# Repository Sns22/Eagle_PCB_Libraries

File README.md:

my_Eagle_PCB_Libraries
======================

Set of Eagle libraries collected all over the internet. This is a set of Eagle libraries I have downloaded from whereever I could get them from. Some libraries from popular vendors such as LEMO, Farnell, ADAfruit, Sparkfun. There are also ulp and scr files in here.

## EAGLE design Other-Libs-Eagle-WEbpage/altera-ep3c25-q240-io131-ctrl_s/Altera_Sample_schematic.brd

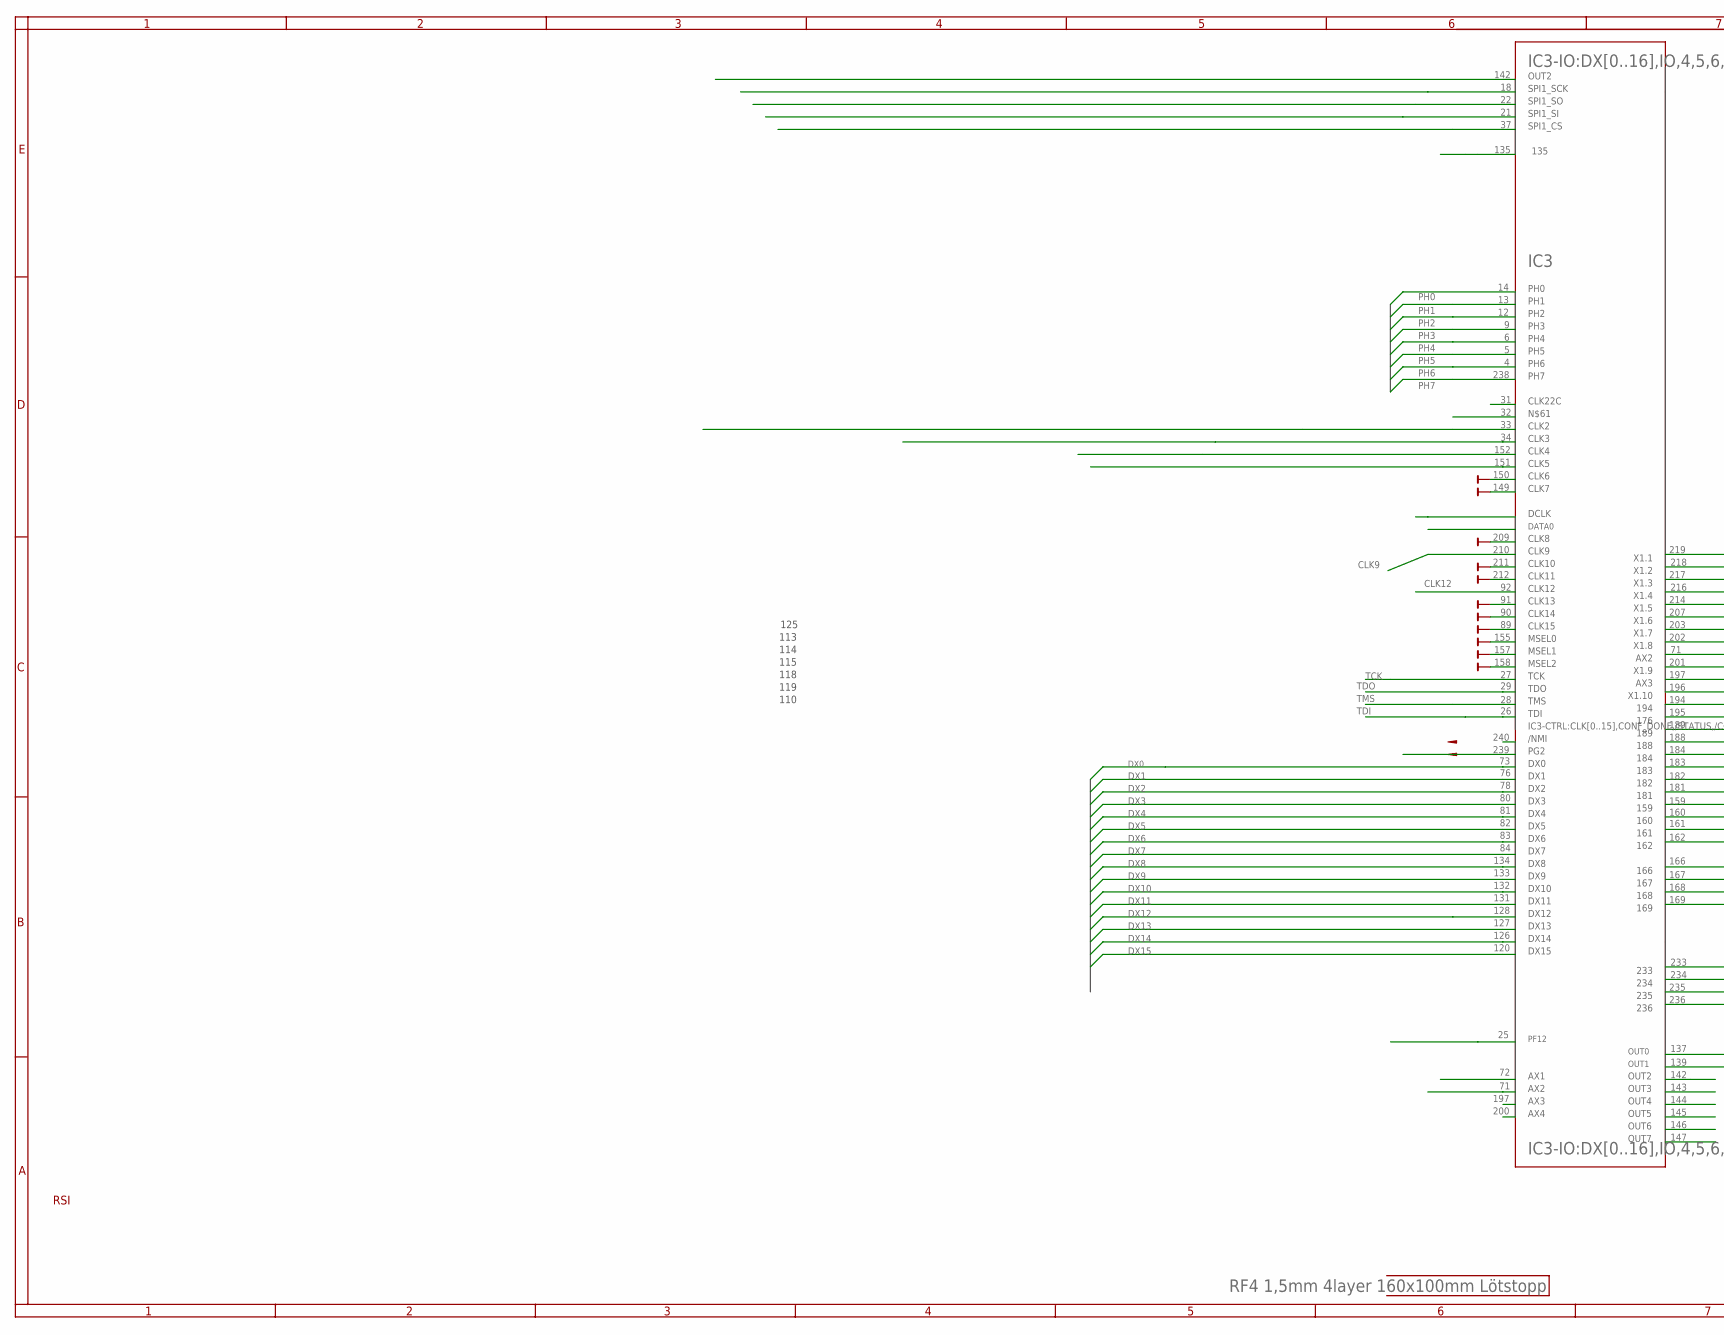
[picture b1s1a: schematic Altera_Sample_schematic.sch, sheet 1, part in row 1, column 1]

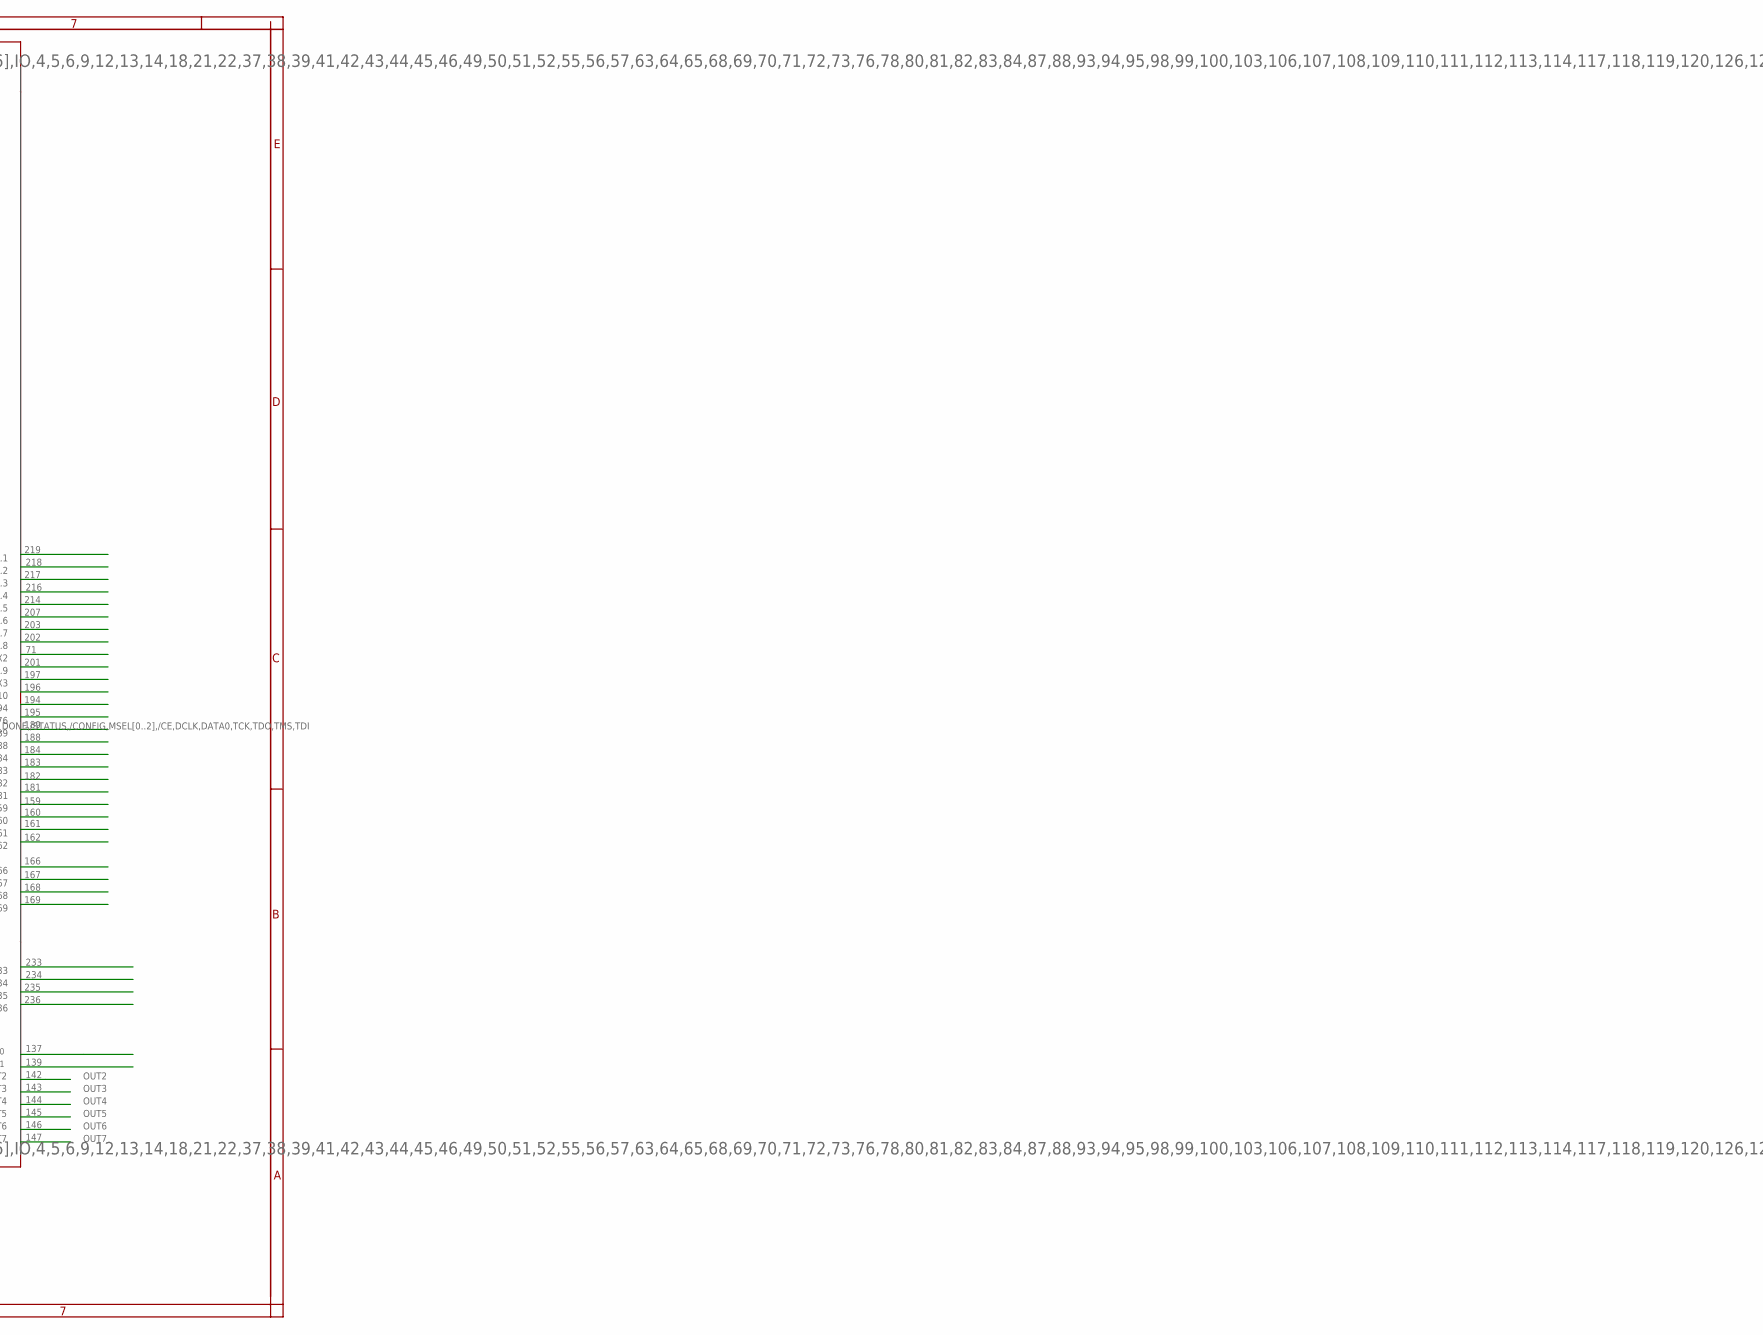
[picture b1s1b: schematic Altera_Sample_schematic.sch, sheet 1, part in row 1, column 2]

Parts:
PCB: RF4 1,5mm 4layer 160x100mm Lötstopp; PCB

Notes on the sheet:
RSI
110
119
118
115
114
113
125
IC3
134
133
132
131
128
127
126
120
240
239
197
200
142
135
238
158
157
155
212
211
210
209
149
150
151
152
137
139
143
144
145

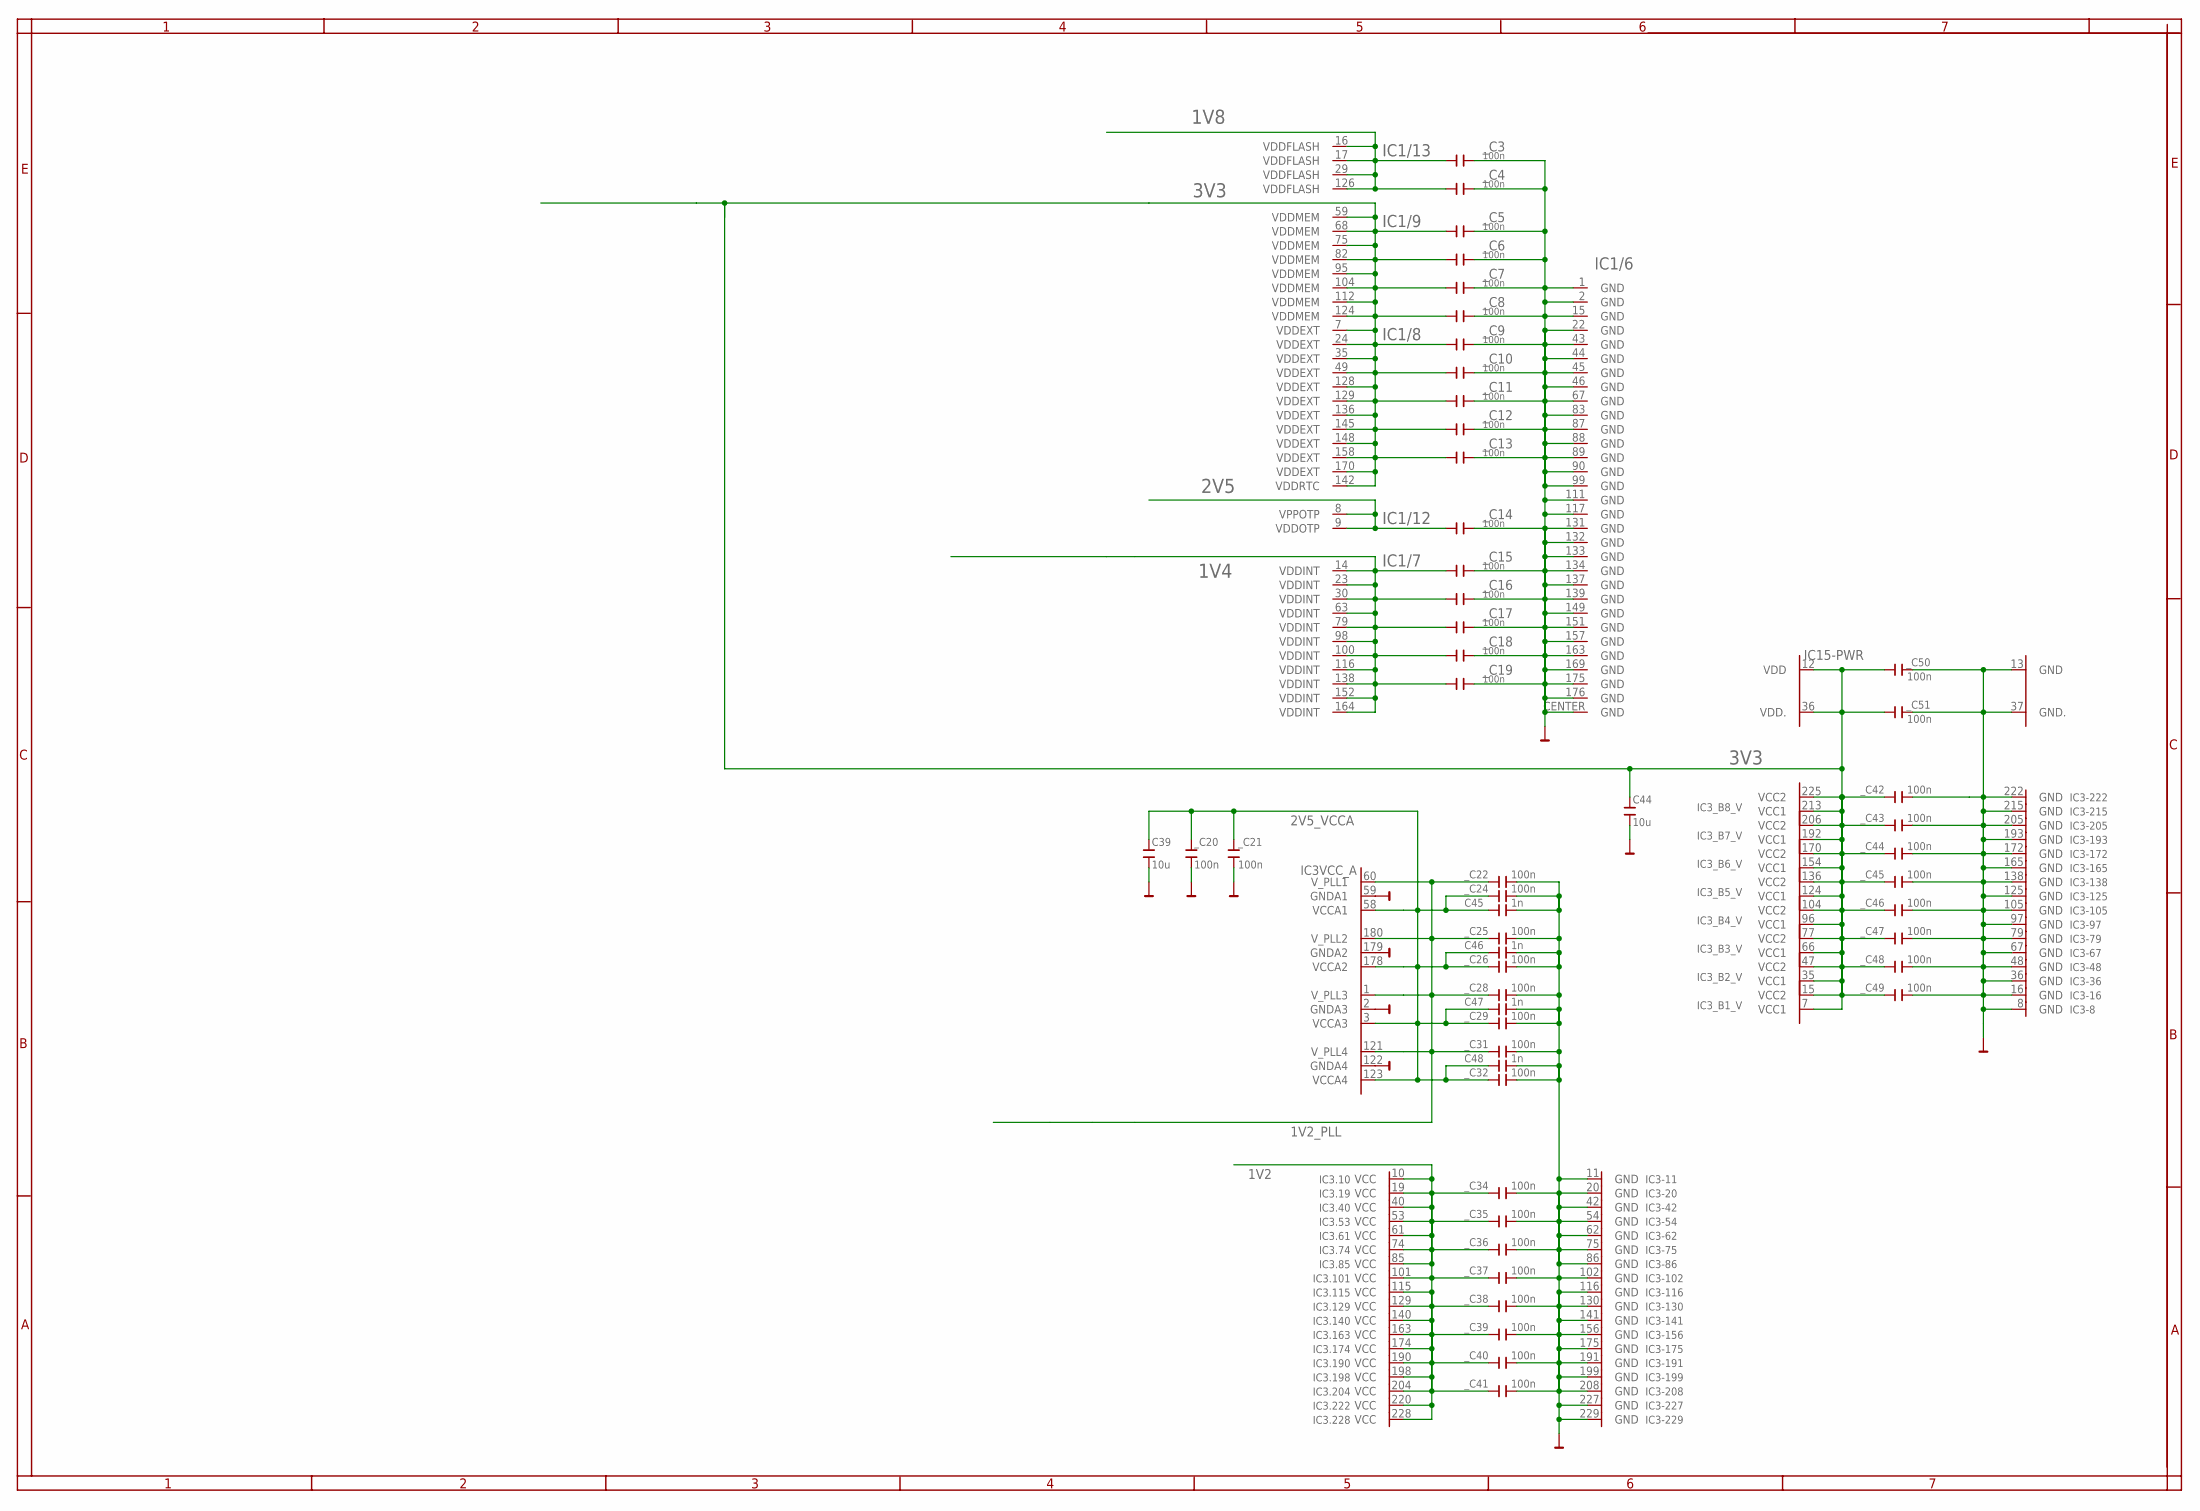
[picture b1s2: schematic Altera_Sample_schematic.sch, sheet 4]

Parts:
C39, C44: 10u; C1210K
C45, C46, C47, C48: 1n; C0805
IC1: ADSP-BF514_PART; LQFP-176+GND
IC3: EP3C25-Q240-IO131; PQFP240
IC15: IS62WV102416ALL; TSOP1-12X20
_C3, _C4, _C5, _C6, _C7, _C8, _C9, _C10, _C11, _C12, _C13, _C14, _C15, _C16, _C17, _C18, _C19, _C20, _C21, _C22, _C24, _C25, _C26, _C28, _C29, _C31, _C32, _C34, _C35, _C36, _C37, _C38, _C39, _C40, _C41, _C42, _C43, _C44, _C45, _C46, _C47, _C48, _C49, _C50, _C51: 100n; C0805

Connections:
1V2: IC3.10 (VCC), IC3.19 (VCC), IC3.40 (VCC), IC3.53 (VCC), IC3.61 (VCC), IC3.74 (VCC), IC3.85 (VCC), IC3.101 (VCC), IC3.115 (VCC), IC3.129 (VCC), IC3.140 (VCC), IC3.163 (VCC), IC3.174 (VCC), IC3.190 (VCC), IC3.198 (VCC), IC3.204 (VCC), IC3.220 (VCC), IC3.228 (VCC), _C34.2, _C35.2, _C36.2, _C37.2, _C38.2, _C39.2, _C40.2, _C41.2
1V2_PLL: IC3.1 (V_PLL3), IC3.60 (V_PLL1), IC3.121 (V_PLL4), IC3.180 (V_PLL2), _C22.2, _C25.2, _C28.2, _C31.2
1V4: IC1.14 (VDDINT), IC1.23 (VDDINT), IC1.30 (VDDINT), IC1.63 (VDDINT), IC1.79 (VDDINT), IC1.98 (VDDINT), IC1.100 (VDDINT), IC1.116 (VDDINT), IC1.138 (VDDINT), IC1.152 (VDDINT), IC1.164 (VDDINT), _C15.1, _C16.1, _C17.1, _C18.1, _C19.1
1V8: IC1.16 (VDDFLASH), IC1.17 (VDDFLASH), IC1.29 (VDDFLASH), IC1.126 (VDDFLASH), _C3.1, _C4.1
2V5: IC1.8 (VPPOTP), IC1.9 (VDDOTP), _C14.1
2V5_VCCA: C39.2, C45.2, C46.2, C47.2, C48.2, IC3.3 (VCCA3), IC3.58 (VCCA1), IC3.123 (VCCA4), IC3.178 (VCCA2), _C20.2, _C21.2, _C24.2, _C26.2, _C29.2, _C32.2
3V3: C44.2, IC1.7 (VDDEXT), IC1.24 (VDDEXT), IC1.35 (VDDEXT), IC1.49 (VDDEXT), IC1.59 (VDDMEM), IC1.68 (VDDMEM), IC1.75 (VDDMEM), IC1.82 (VDDMEM), IC1.95 (VDDMEM), IC1.104 (VDDMEM), IC1.112 (VDDMEM), IC1.124 (VDDMEM), IC1.128 (VDDEXT), IC1.129 (VDDEXT), IC1.136 (VDDEXT), IC1.142 (VDDRTC), IC1.145 (VDDEXT), IC1.148 (VDDEXT), IC1.158 (VDDEXT), IC1.170 (VDDEXT), IC3.7 (VCC1), IC3.15 (VCC2), IC3.35 (VCC1), IC3.47 (VCC2), IC3.66 (VCC1), IC3.77 (VCC2), IC3.96 (VCC1), IC3.104 (VCC2), IC3.124 (VCC1), IC3.136 (VCC2), IC3.154 (VCC1), IC3.170 (VCC2), IC3.192 (VCC1), IC3.206 (VCC2), IC3.213 (VCC1), IC3.225 (VCC2), IC15.12 (VDD), IC15.36 (VDD.), _C5.1, _C6.1, _C7.1, _C8.1, _C9.1, _C10.1, _C11.1, _C12.1, _C13.1, _C42.2, _C43.2, _C44.2, _C45.2, _C46.2, _C47.2, _C48.2, _C49.2, _C50.1, _C51.1
BMODE0: IC1.42 (BMODE0)
BMODE1: IC1.41 (BMODE1)
BMODE2: IC1.40 (BMODE2)
GND: C39.1, C44.1, C45.1, C46.1, C47.1, C48.1, IC1.1 (GND), IC1.2 (GND), IC1.15 (GND), IC1.22 (GND), IC1.43 (GND), IC1.44 (GND), IC1.45 (GND), IC1.46 (GND), IC1.67 (GND), IC1.83 (GND), IC1.87 (GND), IC1.88 (GND), IC1.89 (GND), IC1.90 (GND), IC1.99 (GND), IC1.111 (GND), IC1.117 (GND), IC1.131 (GND), IC1.132 (GND), IC1.133 (GND), IC1.134 (GND), IC1.137 (GND), IC1.139 (GND), IC1.149 (GND), IC1.151 (GND), IC1.157 (GND), IC1.163 (GND), IC1.169 (GND), IC1.175 (GND), IC1.176 (GND), IC1.CENTER (GND), IC3.2 (GNDA3), IC3.8 (GND), IC3.11 (GND), IC3.16 (GND), IC3.20 (GND), IC3.36 (GND), IC3.42 (GND), IC3.48 (GND), IC3.54 (GND), IC3.59 (GNDA1), IC3.62 (GND), IC3.67 (GND), IC3.75 (GND), IC3.79 (GND), IC3.86 (GND), IC3.97 (GND), IC3.102 (GND), IC3.105 (GND), IC3.116 (GND), IC3.122 (GNDA4), IC3.125 (GND), IC3.130 (GND), IC3.138 (GND), IC3.141 (GND), IC3.156 (GND), IC3.165 (GND), IC3.172 (GND), IC3.175 (GND), IC3.179 (GNDA2), IC3.191 (GND), IC3.193 (GND), IC3.199 (GND), IC3.205 (GND), IC3.208 (GND), IC3.215 (GND), IC3.222 (GND), IC3.227 (GND), IC3.229 (GND), IC15.13 (GND), IC15.37 (GND.), _C3.2, _C4.2, _C5.2, _C6.2, _C7.2, _C8.2, _C9.2, _C10.2, _C11.2, _C12.2, _C13.2, _C14.2, _C15.2, _C16.2, _C17.2, _C18.2, _C19.2, _C20.1, _C21.1, _C22.1, _C24.1, _C25.1, _C26.1, _C28.1, _C29.1, _C31.1, _C32.1, _C34.1, _C35.1, _C36.1, _C37.1, _C38.1, _C39.1, _C40.1, _C41.1, _C42.1, _C43.1, _C44.1, _C45.1, _C46.1, _C47.1, _C48.1, _C49.1, _C50.2, _C51.2; also elsewhere on the board

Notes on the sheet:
IC1/13
IC1/9
IC1/8
IC1/12
IC1/7
IC1/6

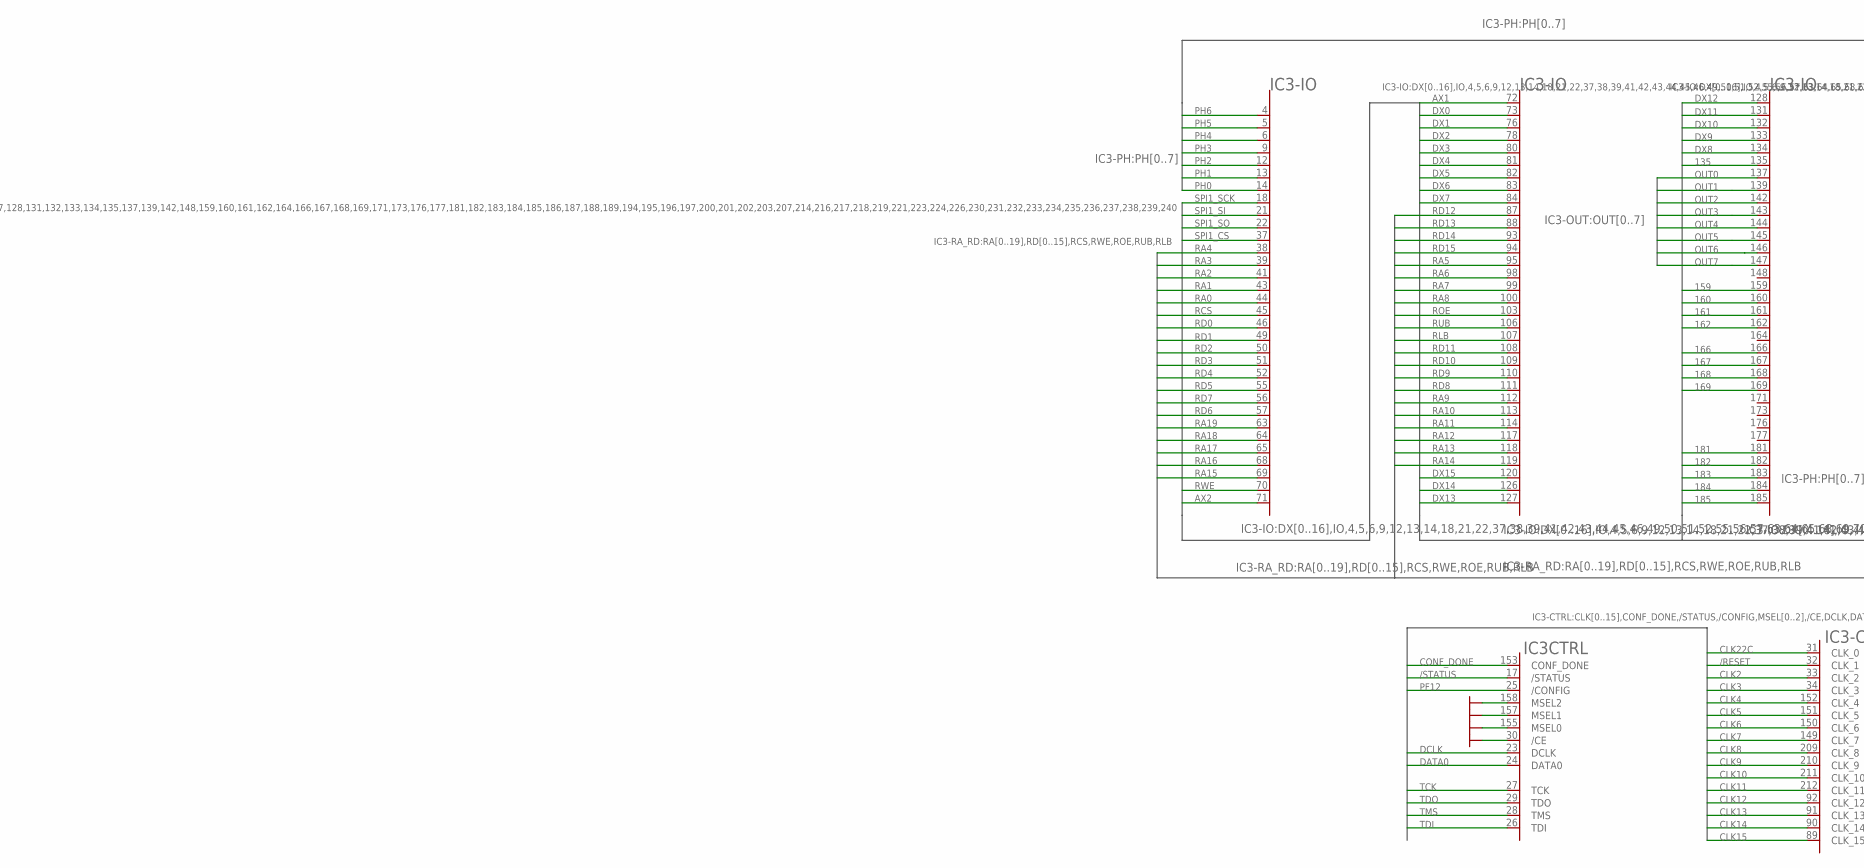
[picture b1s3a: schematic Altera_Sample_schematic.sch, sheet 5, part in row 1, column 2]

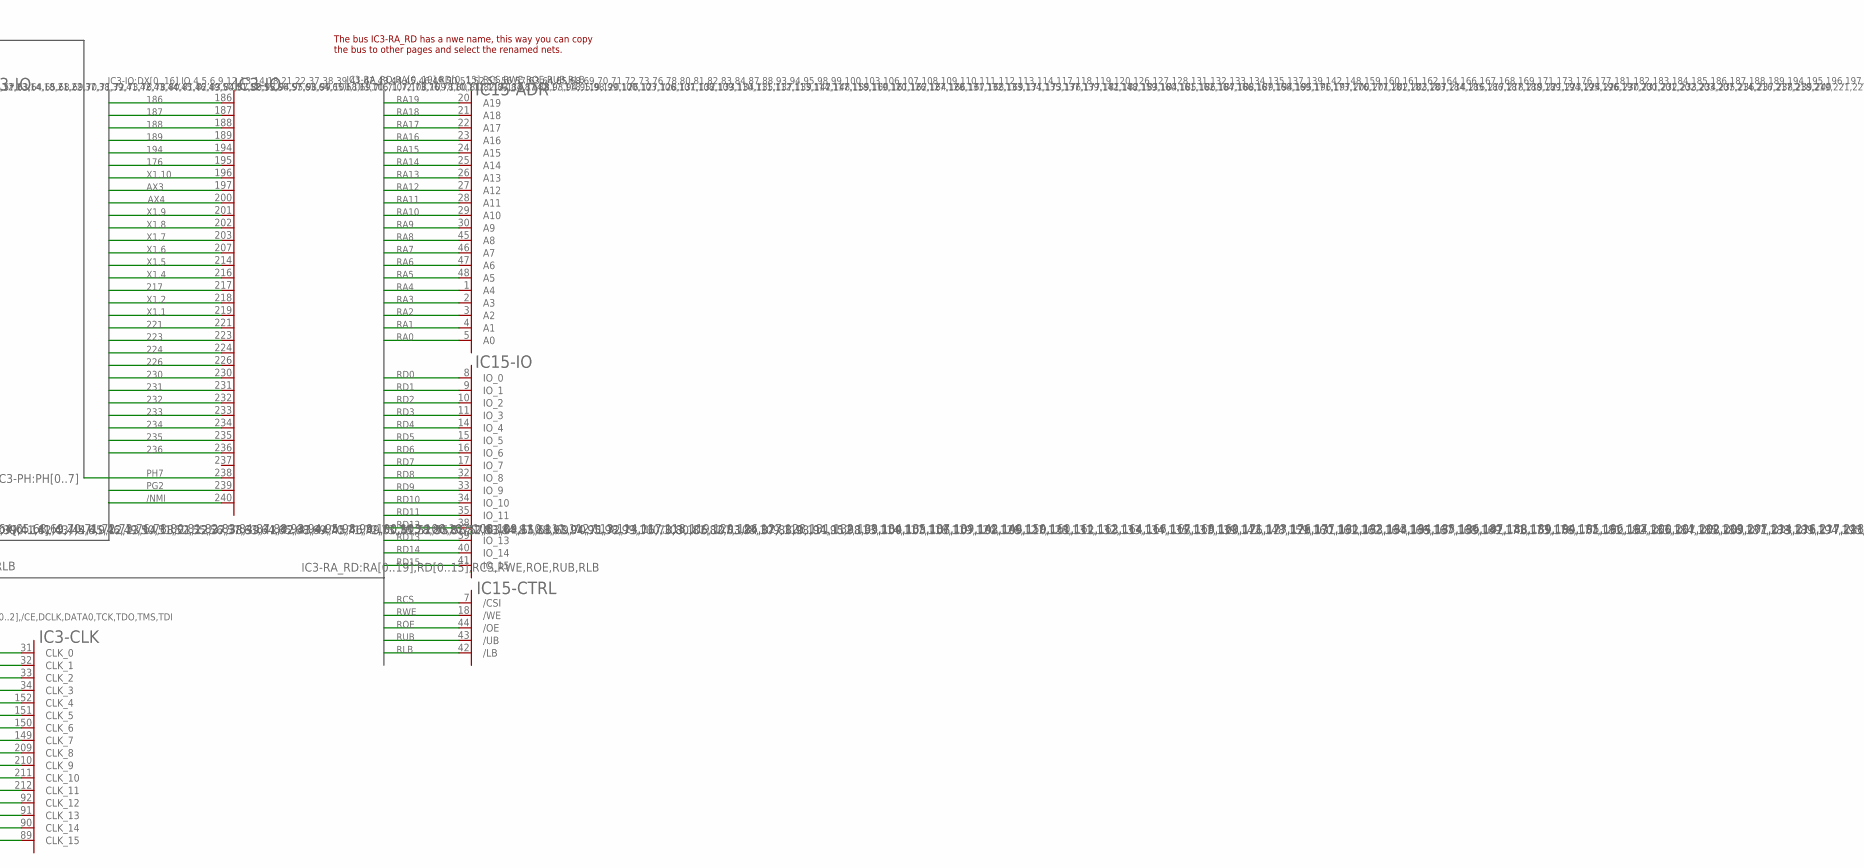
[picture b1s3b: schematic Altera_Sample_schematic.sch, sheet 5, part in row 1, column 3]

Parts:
IC3: EP3C25-Q240-IO131; PQFP240
IC15: IS62WV102416ALL; TSOP1-12X20

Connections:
135: IC3.135 (IO_71)
159: IC3.159 (IO_81)
160: IC3.160 (IO_82)
161: IC3.161 (IO_83)
162: IC3.162 (IO_84)
166: IC3.166 (IO_86)
167: IC3.167 (IO_87)
168: IC3.168 (IO_88)
169: IC3.169 (IO_89)
176: IC3.195 (IO_104)
181: IC3.181 (IO_94)
182: IC3.182 (IO_95)
183: IC3.183 (IO_96)
184: IC3.184 (IO_97)
185: IC3.185 (IO_98)
186: IC3.186 (IO_99)
187: IC3.187 (IO_100)
188: IC3.188 (IO_101)
189: IC3.189 (IO_102)
194: IC3.194 (IO_103)
217: IC3.217 (IO_114)
221: IC3.221 (IO_117)
223: IC3.223 (IO_118)
224: IC3.224 (IO_119)
226: IC3.226 (IO_120)
230: IC3.230 (IO_121)
231: IC3.231 (IO_122)
232: IC3.232 (IO_123)
233: IC3.233 (IO_124)
234: IC3.234 (IO_125)
235: IC3.235 (IO_126)
236: IC3.236 (IO_127)
/NMI: IC3.240 (IO_131)
/RESET: IC3.32 (CLK_1)
/STATUS: IC3.17 (/STATUS)
AX1: IC3.72 (IO_33)
AX2: IC3.71 (IO_32)
AX3: IC3.197 (IO_106)
AX4: IC3.200 (IO_107)
CLK2: IC3.33 (CLK_2)
CLK3: IC3.34 (CLK_3)
CLK4: IC3.152 (CLK_4)
CLK5: IC3.151 (CLK_5)
CLK6: IC3.150 (CLK_6)
CLK7: IC3.149 (CLK_7)
CLK8: IC3.209 (CLK_8)
CLK9: IC3.210 (CLK_9)
CLK10: IC3.211 (CLK_10)
CLK11: IC3.212 (CLK_11)
CLK12: IC3.92 (CLK_12)
CLK13: IC3.91 (CLK_13)
CLK14: IC3.90 (CLK_14)
CLK15: IC3.89 (CLK_15)
CLK22C: IC3.31 (CLK_0)
CONF_DONE: IC3.153 (CONF_DONE)
DATA0: IC3.24 (DATA0)
DCLK: IC3.23 (DCLK)
DX0: IC3.73 (IO_34)
DX1: IC3.76 (IO_35)
DX2: IC3.78 (IO_36)
DX3: IC3.80 (IO_37)
DX4: IC3.81 (IO_38)
DX5: IC3.82 (IO_39)
DX6: IC3.83 (IO_40)
DX7: IC3.84 (IO_41)
DX8: IC3.134 (IO_70)
DX9: IC3.133 (IO_69)
DX10: IC3.132 (IO_68)
DX11: IC3.131 (IO_67)
DX12: IC3.128 (IO_66)
DX13: IC3.127 (IO_65)
DX14: IC3.126 (IO_64)
DX15: IC3.120 (IO_63)
GND: IC3.30 (/CE), IC3.155 (MSEL0), IC3.157 (MSEL1), IC3.158 (MSEL2); also elsewhere on the board
OUT0: IC3.137 (IO_72)
OUT1: IC3.139 (IO_73)
OUT2: IC3.142 (IO_74)
OUT3: IC3.143 (IO_75)
OUT4: IC3.144 (IO_76)
OUT5: IC3.145 (IO_77)
OUT6: IC3.146 (IO_78)
OUT7: IC3.147 (IO_79)
PF12: IC3.25 (/CONFIG)
PG2: IC3.239 (IO_130)
PH0: IC3.14 (IO_7)
PH1: IC3.13 (IO_6)
PH2: IC3.12 (IO_5)
PH3: IC3.9 (IO_4)
PH4: IC3.6 (IO_3)
PH5: IC3.5 (IO_2)
PH6: IC3.4 (IO_1)
PH7: IC3.238 (IO_129)
RA0: IC3.44 (IO_16), IC15.5 (A0)
RA1: IC3.43 (IO_15), IC15.4 (A1)
RA2: IC3.41 (IO_14), IC15.3 (A2)
RA3: IC3.39 (IO_13), IC15.2 (A3)
RA4: IC3.38 (IO_12), IC15.1 (A4)
RA5: IC3.95 (IO_46), IC15.48 (A5)
RA6: IC3.98 (IO_47), IC15.47 (A6)
RA7: IC3.99 (IO_48), IC15.46 (A7)
RA8: IC3.100 (IO_49), IC15.45 (A8)
RA9: IC3.112 (IO_57), IC15.30 (A9)
RA10: IC3.113 (IO_58), IC15.29 (A10)
RA11: IC3.114 (IO_59), IC15.28 (A11)
RA12: IC3.117 (IO_60), IC15.27 (A12)
RA13: IC3.118 (IO_61), IC15.26 (A13)
RA14: IC3.119 (IO_62), IC15.25 (A14)
RA15: IC3.69 (IO_30), IC15.24 (A15)
RA16: IC3.68 (IO_29), IC15.23 (A16)
RA17: IC3.65 (IO_28), IC15.22 (A17)
RA18: IC3.64 (IO_27), IC15.21 (A18)
RA19: IC3.63 (IO_26), IC15.20 (A19)
RCS: IC3.45 (IO_17), IC15.7 (/CSI)
RD0: IC3.46 (IO_18), IC15.8 (IO_0)
RD1: IC3.49 (IO_19), IC15.9 (IO_1)
RD2: IC3.50 (IO_20), IC15.10 (IO_2)
RD3: IC3.51 (IO_21), IC15.11 (IO_3)
RD4: IC3.52 (IO_22), IC15.14 (IO_4)
RD5: IC3.55 (IO_23), IC15.15 (IO_5)
RD6: IC3.57 (IO_25), IC15.16 (IO_6)
RD7: IC3.56 (IO_24), IC15.17 (IO_7)
RD8: IC3.111 (IO_56), IC15.32 (IO_8)
RD9: IC3.110 (IO_55), IC15.33 (IO_9)
RD10: IC3.109 (IO_54), IC15.34 (IO_10)
RD11: IC3.108 (IO_53), IC15.35 (IO_11)
RD12: IC3.87 (IO_42), IC15.38 (IO_12)
RD13: IC3.88 (IO_43), IC15.39 (IO_13)
RD14: IC3.93 (IO_44), IC15.40 (IO_14)
RD15: IC3.94 (IO_45), IC15.41 (IO_15)
RLB: IC3.107 (IO_52), IC15.42 (/LB)
ROE: IC3.103 (IO_50), IC15.44 (/OE)
RUB: IC3.106 (IO_51), IC15.43 (/UB)
RWE: IC3.70 (IO_31), IC15.18 (/WE)
SPI1_CS: IC3.37 (IO_11)
SPI1_SCK: IC3.18 (IO_8)
SPI1_SI: IC3.21 (IO_9)
SPI1_SO: IC3.22 (IO_10)
TCK: IC3.27 (TCK)
TDI: IC3.26 (TDI)
TDO: IC3.29 (TDO)
TMS: IC3.28 (TMS)
X1.1: IC3.219 (IO_116)
X1.2: IC3.218 (IO_115)
X1.4: IC3.216 (IO_113)
X1.5: IC3.214 (IO_112)
X1.6: IC3.207 (IO_111)
X1.7: IC3.203 (IO_110)
X1.8: IC3.202 (IO_109)
X1.9: IC3.201 (IO_108)
X1.10: IC3.196 (IO_105)

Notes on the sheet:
IC3-IO
The bus IC3-RA_RD has a nwe name, this way you can copy the bus to other pages and select the renamed nets.

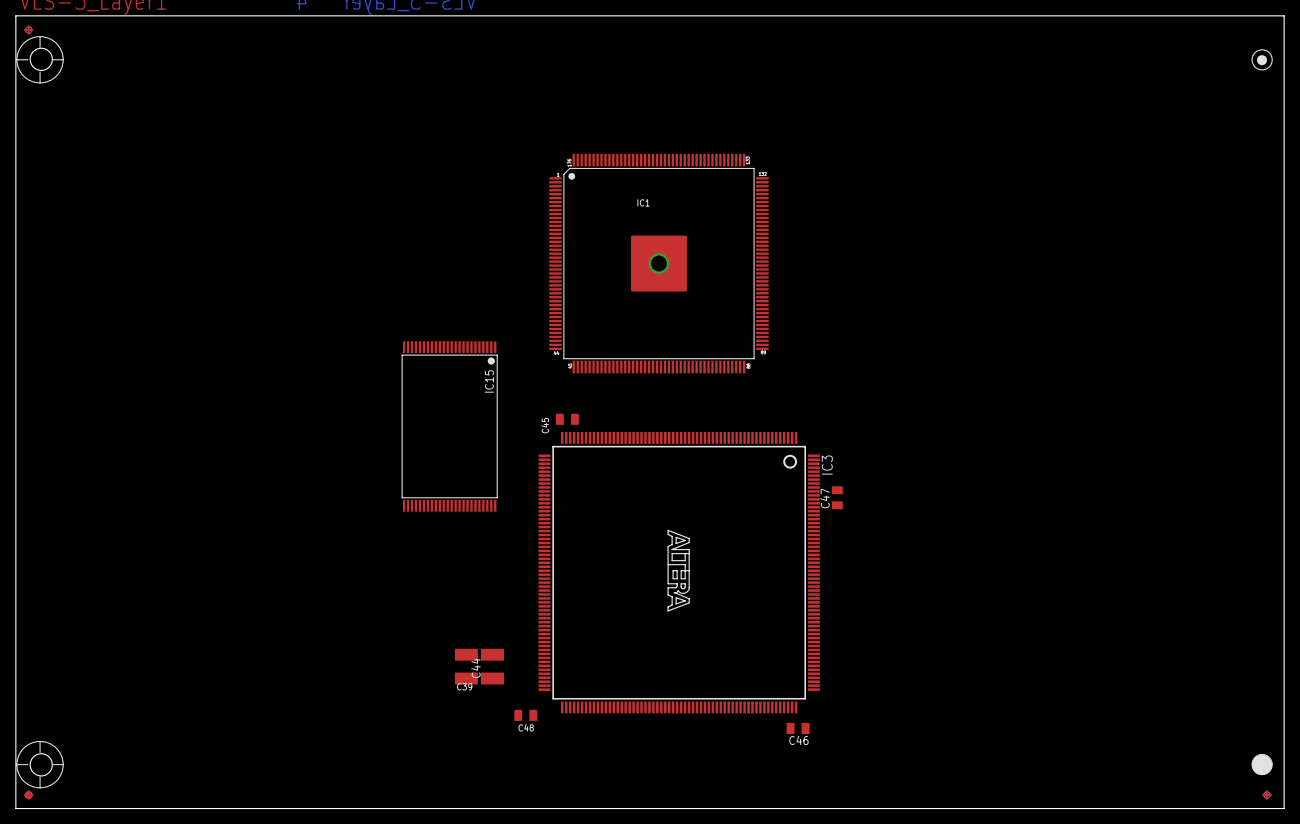
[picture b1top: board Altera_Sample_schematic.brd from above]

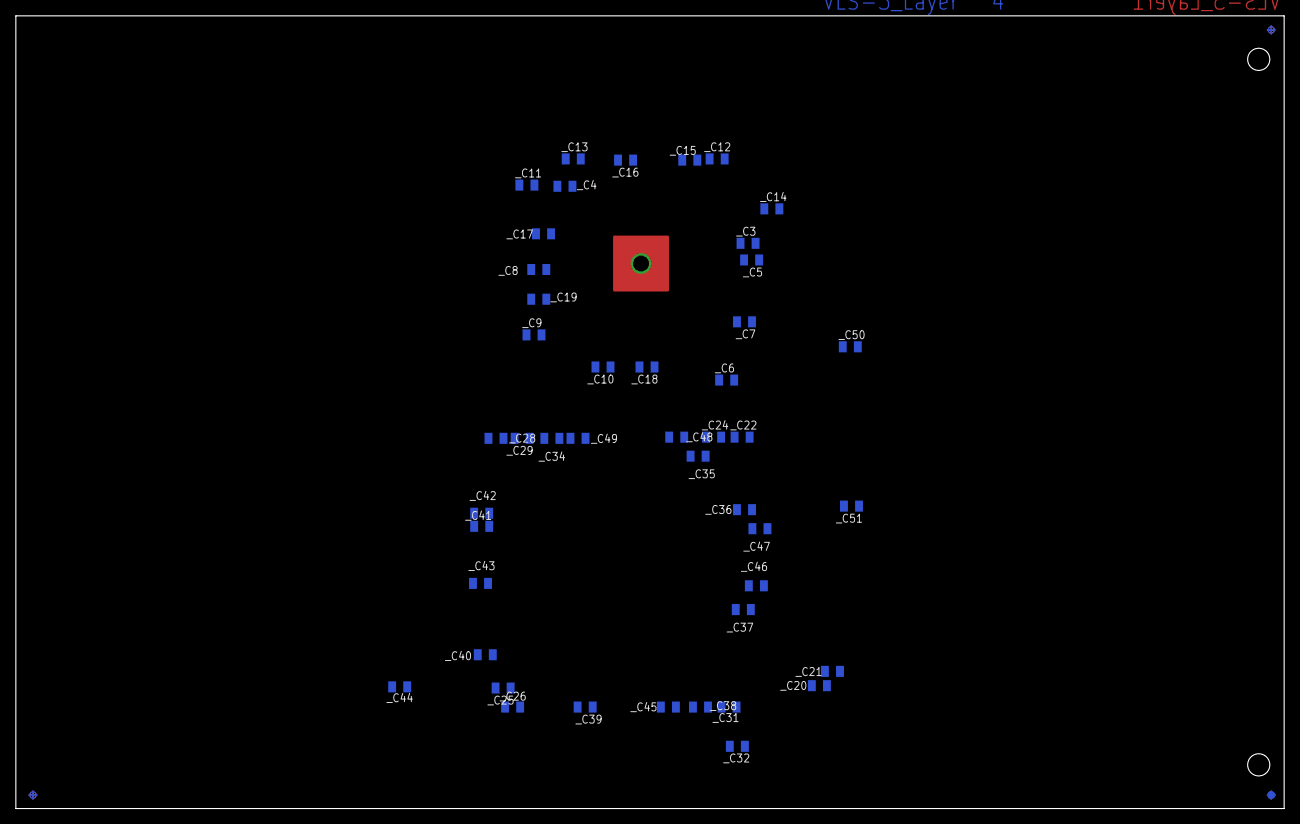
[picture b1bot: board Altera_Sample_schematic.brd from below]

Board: 4 copper layers, 160.0 x 100.0 mm, 56 parts (45 on the bottom side), 49 nets.

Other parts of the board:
U$1: EURO

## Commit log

2013-07-11 Eagle PCB design Libraries
    With Lemo and SMA connector libraries.
2013-07-11 setup
2013-07-11 Eagle PCB Libraries
2013-07-11 Eagle
